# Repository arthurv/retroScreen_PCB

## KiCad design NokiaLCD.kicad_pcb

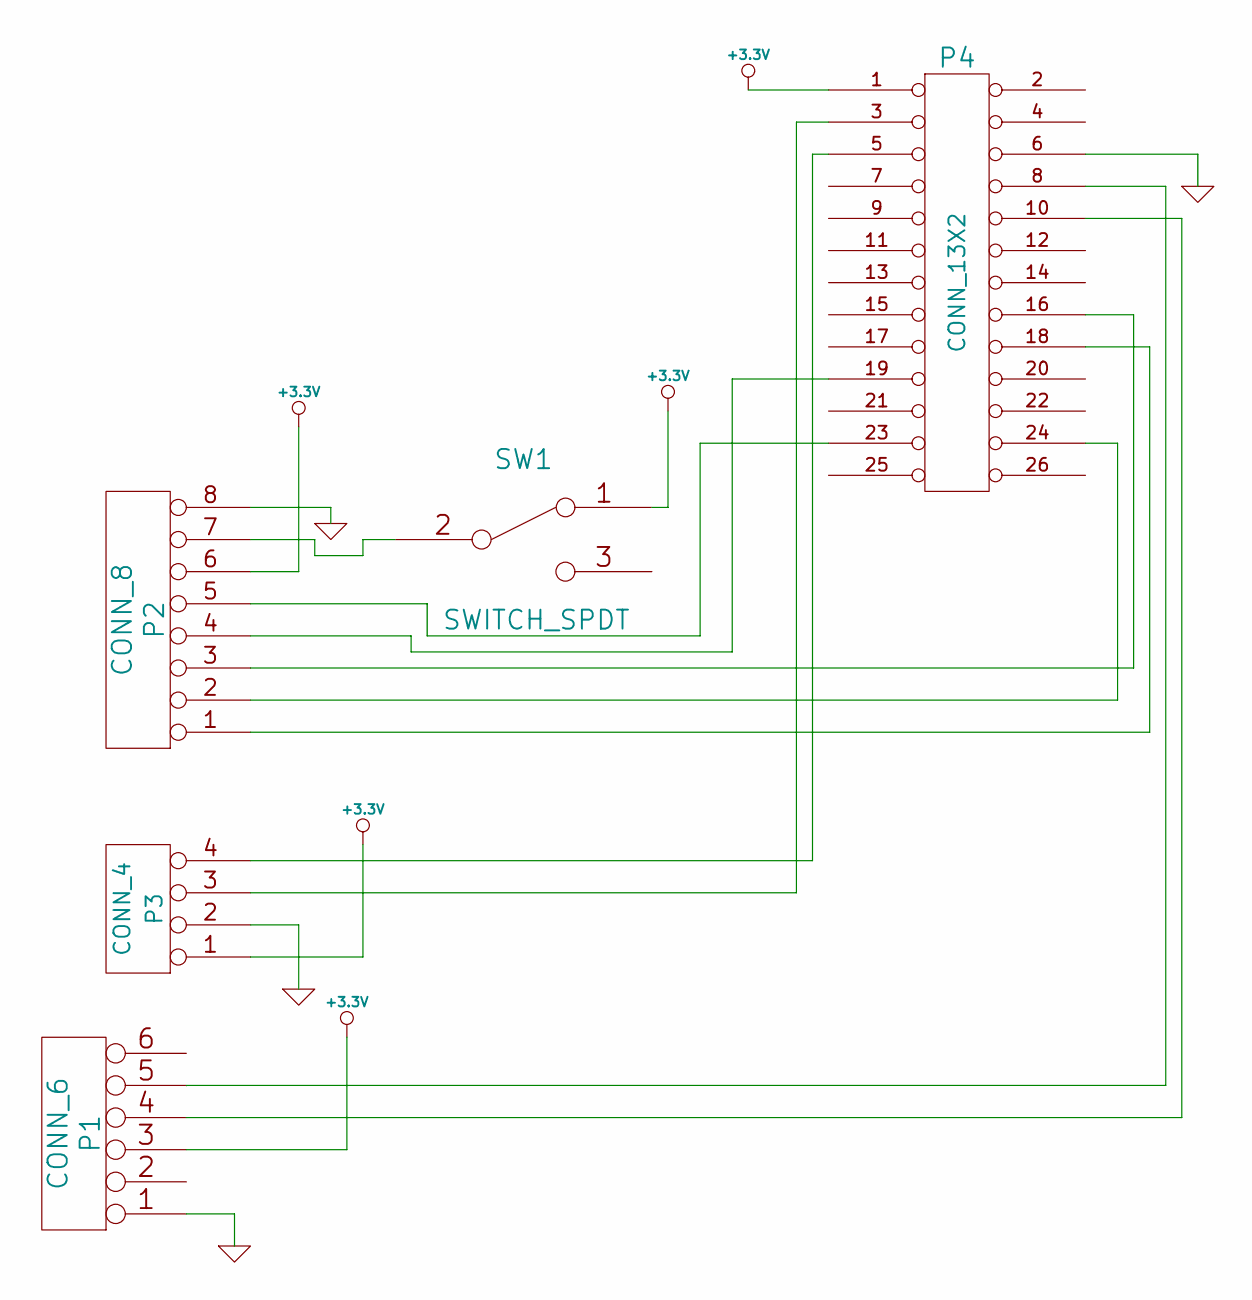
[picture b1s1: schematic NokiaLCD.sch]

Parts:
P1: CONN_6
P2: CONN_8
P3: CONN_4
P4: CONN_13X2
SW1: SWITCH_SPDT

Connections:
+3.3V: P1.3, P2.6, P3.1, P4.1, SW1.1
GND: P1.1, P2.8, P3.2, P4.6
unnamed: P2.2, P4.24 (P20)
unnamed: P2.3, P4.16
unnamed: P2.4, P4.19
unnamed: P2.5, P4.23
unnamed: P3.4, P4.5
unnamed: P1.4, P4.10
unnamed: P1.5, P4.8
unnamed: P3.3, P4.3
unnamed: P2.1, P4.18
unnamed: P2.7, SW1.2

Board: 2 copper layers, 5 parts (0 on the bottom side), 12 nets, no tracks yet.

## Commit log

2015-04-05 LCD v0.1 hat sent to OSHPark
2015-04-21 Change GPIO schematic. Backlight switch to 5V.
